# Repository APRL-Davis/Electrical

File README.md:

# Electrical
## NOTE: Legacy(2023-2024) repo - transition all continuing projects away - no new projects
Controls and data acquisition systems for Engine Mu-1+2/test stand Mu-1(v1).

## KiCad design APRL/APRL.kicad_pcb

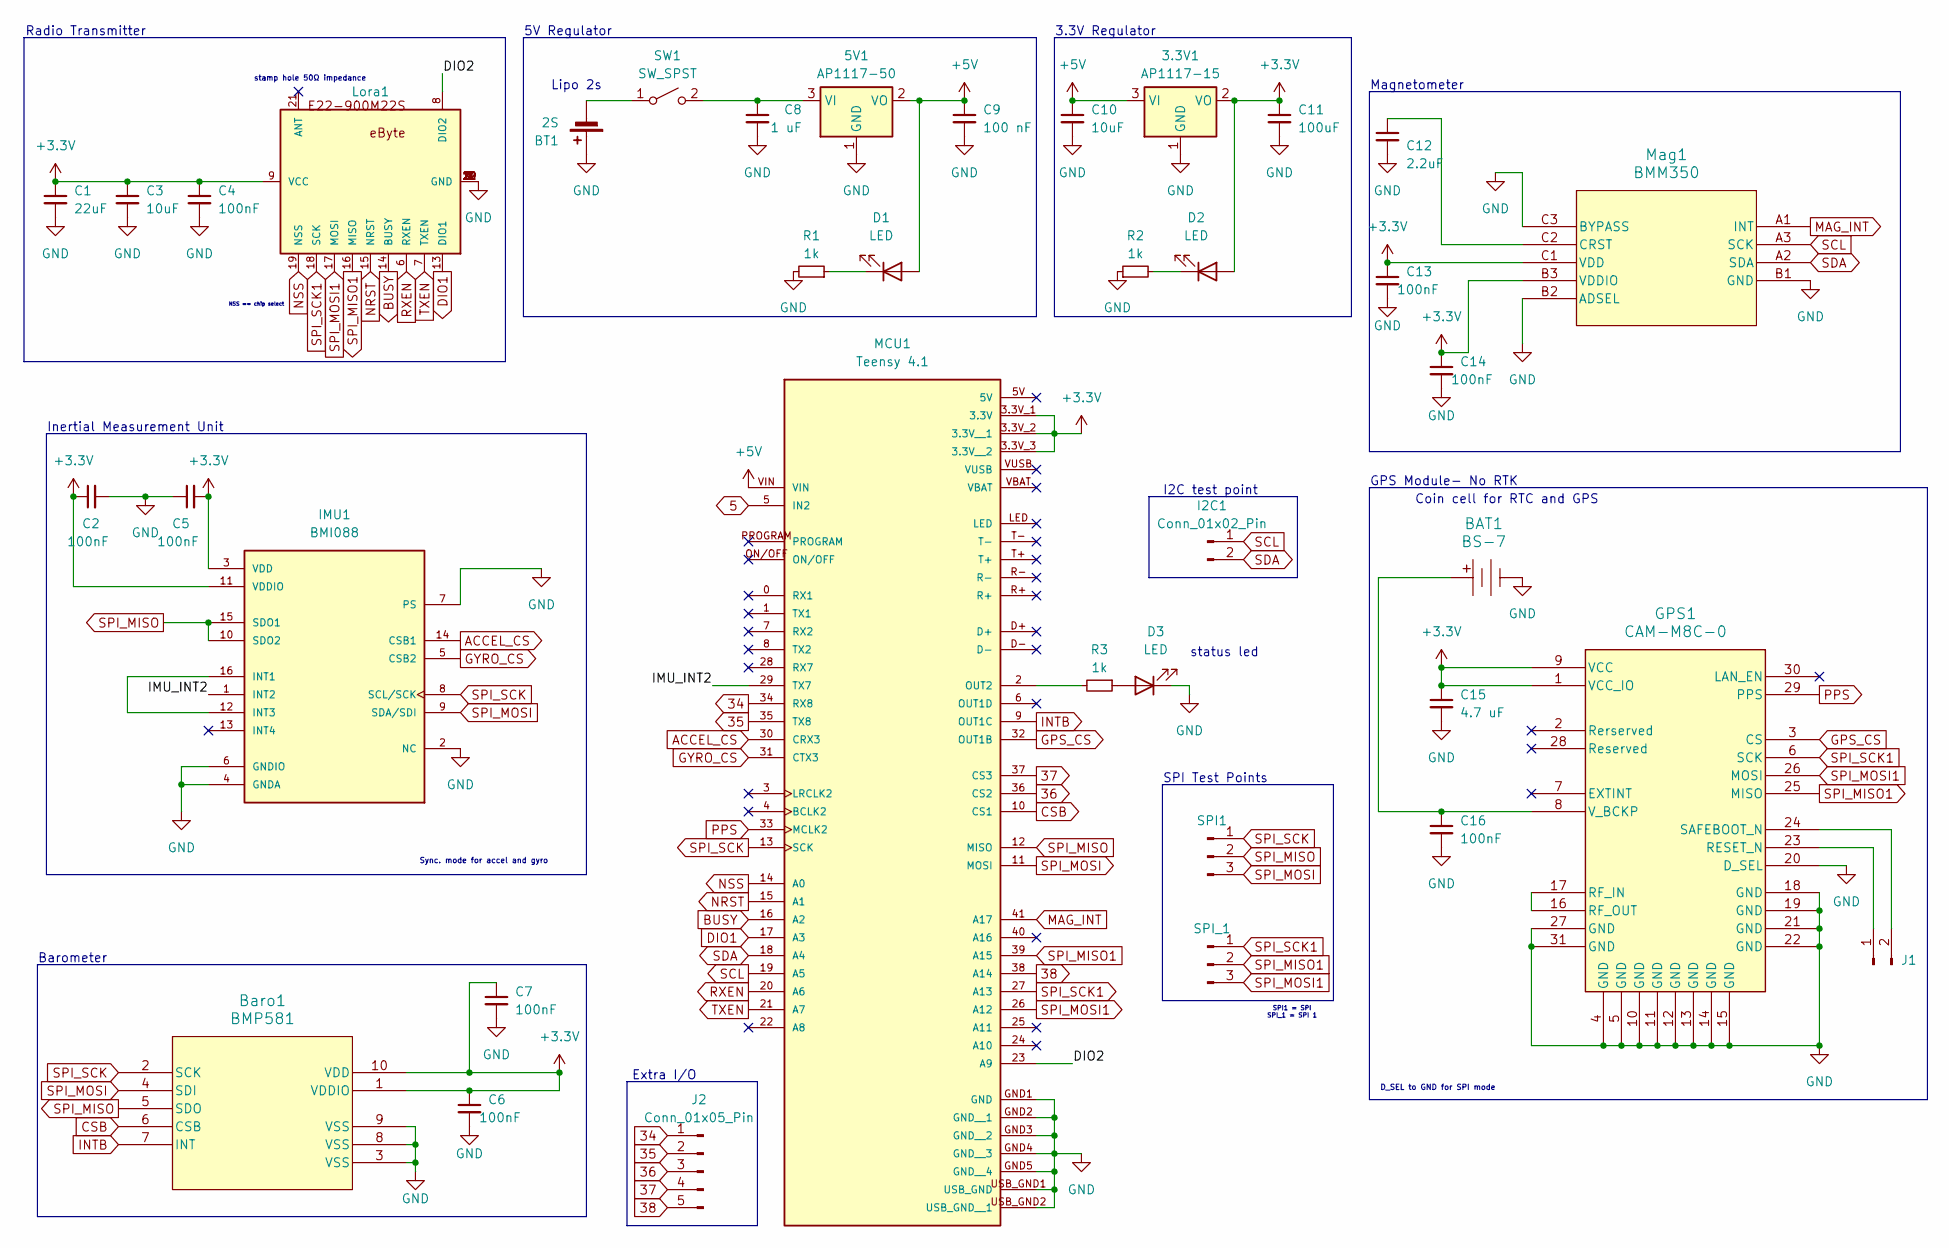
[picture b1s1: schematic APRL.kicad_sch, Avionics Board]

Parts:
3.3V1: AP1117-15; SOT-223-3_TabPin2
5V1: AP1117-50; SOT-223-3_TabPin2
BAT1: BS-7; Battery_Holder_Coin_2032_BS-7; MPN BS-7; Digi-Key_PN BS-7-ND
BT1: 2S; JST_PH_S2B-PH-K_1x02_P2.00mm_Horizontal
Baro1: BMP581; QFN10_BMP581_BOS
C1: 22uF; C_0805_2012Metric
C2, C4, C5, C6, C7, C13, C14, C16: 100nF; C_0603_1608Metric
C3: 10uF; C_0805_2012Metric
C8: 1 uF; C_0603_1608Metric
C9: 100 nF; C_0603_1608Metric
C10: 10uF; C_0603_1608Metric
C11: 100uF; C_0805_2012Metric
C12: 2.2uF; C_0603_1608Metric
C15: 4.7 uF; C_0603_1608Metric
D1, D2, D3: LED; LED_0603_1608Metric
GPS1: CAM-M8C-0; QFN_M8C-0_UBL
I2C1: Conn_01x02_Pin; PinHeader_1x02_P2.54mm_Vertical
IMU1: BMI088; PQFN50P450X300X100-16N
J1: Conn_01x02_Pin; PinHeader_1x02_P2.54mm_Vertical
J2: Conn_01x05_Pin; PinHeader_1x05_P2.54mm_Vertical
Lora1: E22-900M22S
MCU1: Teensy 4.1; Teensy_41; PARTREV 4.1
Mag1: BMM350; BGA9_BMM350_BOS
R1, R2, R3: 1k; R_0603_1608Metric
SPI1: Conn_01x03_Pin; PinHeader_1x03_P2.54mm_Vertical
SPI_1: Conn_01x03_Pin; PinHeader_1x03_P2.54mm_Vertical
SW1: SW_SPST; slide_sw

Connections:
5: MCU1.5 (IN2)
34: J2.1, MCU1.34 (RX8)
35: J2.2, MCU1.35 (TX8)
36: J2.3, MCU1.36 (CS2)
37: J2.4, MCU1.37 (CS3)
38: J2.5, MCU1.38 (A14)
+3.3V: 3.3V1.2 (VO), Baro1.1 (VDDIO), Baro1.10 (VDD), C1.1, C2.1, C3.1, C4.1, C5.2, C6.1, C7.1, C11.1, C13.1, C14.1, C15.1, D2.2 (A), GPS1.1 (VCC_IO), GPS1.9 (VCC), IMU1.3 (VDD), IMU1.11 (VDDIO), Lora1.9 (VCC), MCU1.3.3V_1 (3.3V), MCU1.3.3V_2 (3.3V__1), MCU1.3.3V_3 (3.3V__2), Mag1.B3 (VDDIO), Mag1.C1 (VDD)
+5V: 3.3V1.3 (VI), 5V1.2 (VO), C9.1, C10.1, D1.2 (A), MCU1.VIN
/DIO2: Lora1.8 (DIO2), MCU1.23 (A9)
/IMU_INT2: IMU1.1 (INT2), MCU1.29 (TX7)
ACCEL_CS: IMU1.14 (CSB1), MCU1.30 (CRX3)
BUSY: Lora1.14 (BUSY), MCU1.16 (A2)
CSB: Baro1.6 (CSB), MCU1.10 (CS1)
DIO1: Lora1.13 (DIO1), MCU1.17 (A3)
GND: 3.3V1.1 (GND), 5V1.1 (GND), BAT1.Neg, BT1.1 (+), Baro1.3 (VSS), Baro1.8 (VSS), Baro1.9 (VSS), C1.2, C2.2, C3.2, C4.2, C5.1, C6.2, C7.2, C8.2, C9.2, C10.2, C11.2, C12.2, C13.2, C14.2, C15.2, C16.2, D3.1 (K), GPS1.4 (GND), GPS1.5 (GND), GPS1.10 (GND), GPS1.11 (GND), GPS1.12 (GND), GPS1.13 (GND), GPS1.14 (GND), GPS1.15 (GND), GPS1.18 (GND), GPS1.19 (GND), GPS1.20 (D_SEL), GPS1.21 (GND), GPS1.22 (GND), GPS1.27 (GND), GPS1.31 (GND), IMU1.2 (NC), IMU1.4 (GNDA), IMU1.6 (GNDIO), IMU1.7 (PS), Lora1.1 (GND), Lora1.2 (GND), Lora1.3 (GND), Lora1.4 (GND), Lora1.5 (GND), Lora1.10 (GND), Lora1.11 (GND), Lora1.12 (GND), Lora1.20 (GND), Lora1.22 (GND), MCU1.GND1 (GND), MCU1.GND2 (GND__1), MCU1.GND3 (GND__2), MCU1.GND4 (GND__3), MCU1.GND5 (GND__4), MCU1.USB_GND1 (USB_GND), MCU1.USB_GND2 (USB_GND__1), Mag1.B1 (GND), Mag1.B2 (ADSEL), Mag1.C3 (BYPASS), R1.2, R2.1
GPS_CS: GPS1.3 (CS), MCU1.32 (OUT1B)
GYRO_CS: IMU1.5 (CSB2), MCU1.31 (CTX3)
INTB: Baro1.7 (INT), MCU1.9 (OUT1C)
MAG_INT: MCU1.41 (A17), Mag1.A1 (INT)
NRST: Lora1.15 (NRST), MCU1.15 (A1)
NSS: Lora1.19 (NSS), MCU1.14 (A0)
unnamed: 5V1.3 (VI), C8.1, SW1.2 (B)
unnamed: BT1.2 (-), SW1.1 (A)
unnamed: D1.1 (K), R1.1
unnamed: D2.1 (K), R2.2
unnamed: D3.2 (A), R3.1
unnamed: GPS1.23 (RESET_N), J1.1
unnamed: GPS1.16 (RF_OUT), GPS1.17 (RF_IN)
unnamed: GPS1.24 (SAFEBOOT_N), J1.2
unnamed: BAT1.Pos, C16.1, GPS1.8 (V_BCKP)
unnamed: IMU1.12 (INT3), IMU1.16 (INT1)
unnamed: MCU1.2 (OUT2), R3.2
unnamed: C12.1, Mag1.C2 (CRST)
PPS: GPS1.29 (PPS), MCU1.33 (MCLK2)
RXEN: Lora1.6 (RXEN), MCU1.20 (A6)
SCL: I2C1.1, MCU1.19 (A5), Mag1.A3 (SCK)
SDA: I2C1.2, MCU1.18 (A4), Mag1.A2 (SDA)
SPI_MISO: Baro1.5 (SDO), IMU1.10 (SDO2), IMU1.15 (SDO1), MCU1.12 (MISO), SPI1.2
SPI_MISO1: GPS1.25 (MISO), Lora1.16 (MISO), MCU1.39 (A15), SPI_1.2
SPI_MOSI: Baro1.4 (SDI), IMU1.9 (SDA/SDI), MCU1.11 (MOSI), SPI1.3
SPI_MOSI1: GPS1.26 (MOSI), Lora1.17 (MOSI), MCU1.26 (A12), SPI_1.3
SPI_SCK: Baro1.2 (SCK), IMU1.8 (SCL/SCK), MCU1.13 (SCK), SPI1.1
SPI_SCK1: GPS1.6 (SCK), Lora1.18 (SCK), MCU1.27 (A13), SPI_1.1
TXEN: Lora1.7 (TXEN), MCU1.21 (A7)

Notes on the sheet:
Barometer
SPI Test Points
NSS == chip select
Inertial Measurement Unit
Sync. mode for accel and gyro
Lipo 2s
status led
Coin cell for RTC and GPS
SPI1 = SPI SPI_1 = SPI 1
Magnetometer
3.3V Regulator
GPS Module- No RTK
Radio Transmitter
D_SEL to GND for SPI mode
I2C test point
5V Regulator
Extra I/O
stamp hole 50Ω impedance

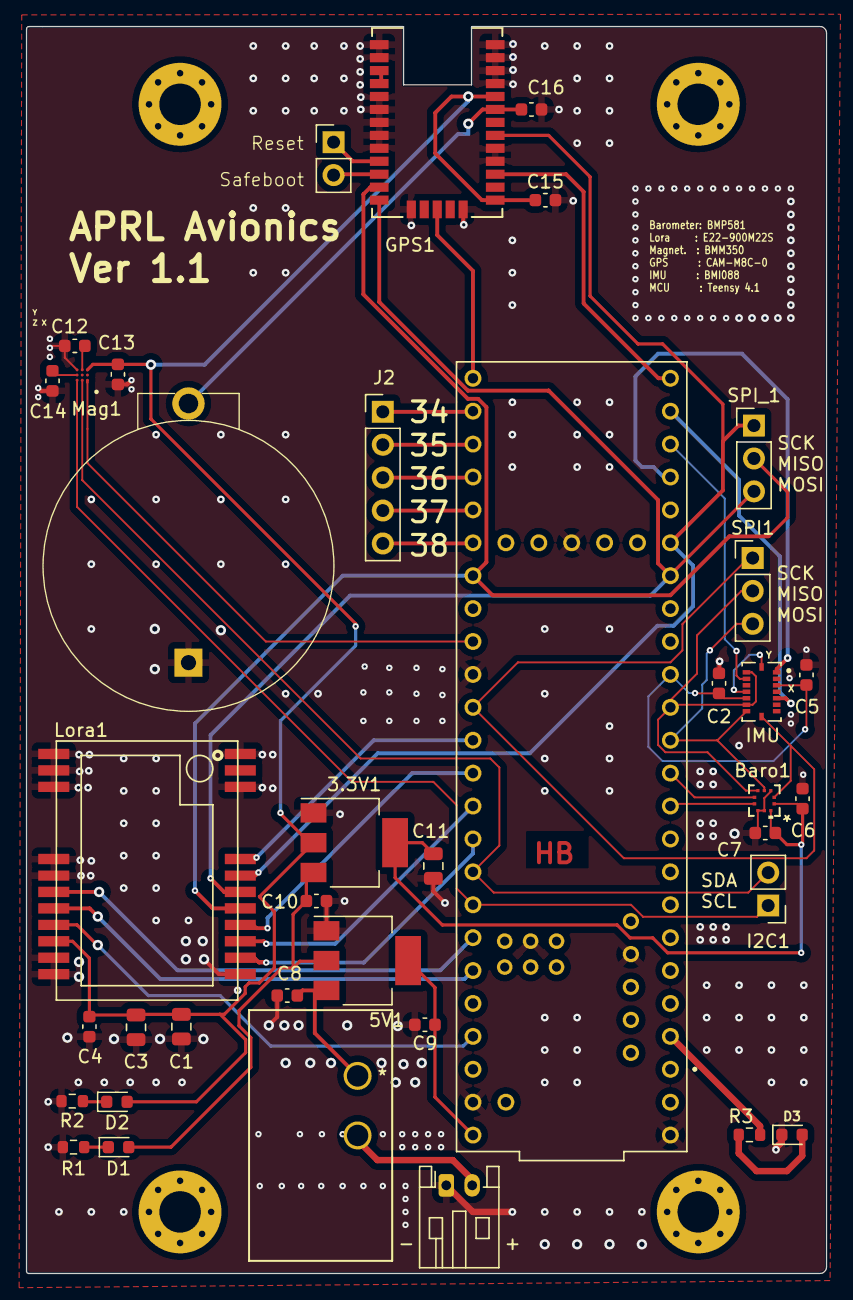
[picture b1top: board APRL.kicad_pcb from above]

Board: 2 copper layers, 61.8 x 96.2 mm, 38 parts (0 on the bottom side), 43 nets.

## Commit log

2023-10-10 Added PID files
2023-10-15 Older works
2023-10-15 add calibration, start, and stop sequence
2023-10-15 add sequences functions to switch statement
2023-10-19 add interrupt routine to control relay sequences
2023-10-19 change pin numbers
2023-10-19 fixed syntax bugs and add random number to print out for testing purposes
2023-10-19 change the reference previous time of millis function when interrupt trigger detected
2023-10-22 fix bugs in switch cases
2023-10-23 Add toggle state through another digital out pins instead of buttons; change interrupt mode to CHANGE from FALLING
2023-10-23 Add serial print statuses
2023-10-31 Modified sensor reading to use interrupts
    - Added a timer with ISR that sets a boolean flag to indicate if the main loop should read in the sensors or not.
    - Modified the end of loop delay from 10 milliseconds (~10 sensor readings) down to 50 microseconds (enough time that the idle process can still run if there is one on Teensy)
2023-11-05 new pin assignments
2023-11-10 upload old backend code
2023-11-14 Set up header file and basic functions for ADS1256
2023-11-19 unimportant change. Baud rate is ignored by Teensy. Actual rate is USB speed.
2023-11-20 starting on sensor struct type
2023-11-20 modifications to sensor reads...
2023-11-20 Added sensor configuration and types
    Also moved the Master.ino file into an appropriately named folder for the Arduino IDE.
    Made a number of updates to the code so that it will compile. No guarantees that it will run correctly.
    Also setup the data packet structures.
2023-11-21 minor structure fixes
2023-12-03 consolidate adc and relay control code
2023-12-03 folder organization
2024-01-08 fixed interrupt, where serial messes with SPI transfer
2024-01-10 fixed serial lagging issue. Make sure serial.read and parseInt occur after serial available
2024-01-17 adding no interrupts during spi transfer
2024-01-19 change data rate to 2000
2024-01-21 01/21/2024 Added purge valve but slow serial again
2024-01-21 Clarify relay and sequences states
2024-01-22 01/22/2024 Updated sequences to factor in new explicit state changes from #9ae741e
2024-01-30 avionics schematics
2024-01-30 Updated Teensy code with changes from #9ae741 (#5)
    * 01/21/2024 Added purge valve but slow serial again
    * 01/22/2024 Updated sequences to factor in new explicit state changes from #9ae741e
2024-02-05 fixed purge timing
2024-02-06 integrating udp and data packinging code from Ben
2024-02-11 Move data transmission to udp. Convert to micro volts and truncate to avoid fixed point.
2024-02-12 add kero scale
2024-02-13 automatically calculate readings per packet based on udp frequency, total sps, and number of sensors. Get rid of sensorData ID
2024-02-19 add time stamps using time library. Mirror commands to main branch. Accept incoming UDP packet for command instead of using Serial. Set port to 21 for standard FTP.
2024-02-24 switch to QNEthernet library and set up python script for client side
2024-02-24 use memset instead of pointer address for udp.begin
2024-02-25 import ti example library template
2024-02-25 update gitignore
2024-02-25 cleanup main
2024-02-25 add link status check in setup
2024-02-25 integrate UDP to main wwith dummy test data
2024-02-25 complete hal.h for teensy, hal.c done up to getStart
2024-02-25 apparently i didn't push
2024-02-27 finish hal.c
2024-02-27 finished modifying library
2024-02-28 cleanup also rename c to cpp
2024-03-01 parse command inputs from udp; add depressurize command; removes depressurize from purge; remove auto purge from fire sequence.
2024-03-06 disable serial check loop to prevent blocking when not connected to computer
2024-03-06 send back valve states
2024-03-06 get rid of dangling pointer in the conversion method. Dynamically allocate memory outside and pass into the function so it doesn't self destruct
2024-03-06 add check sum to detect valve state changes
2024-03-07 attempt merging devop - add static fire mvp changes (#7)
    * integrating udp and data packinging code from Ben
    * Move data transmission to udp. Convert to micro volts and truncate to avoid fixed point.
    * add kero scale
    * automatically calculate readings per packet based on udp frequency, total sps, and number of sensors. Get rid of sensorData ID
    * add time stamps using time library. Mirror commands to main branch. Accept incoming UDP packet for command instead of using Serial. Set port to 21 for standard FTP.
    * switch to QNEthernet library and set up python script for client side
2024-03-07 get rid of checksum loop that detect valve state changes. Directly detect changes when relay is toggle or sequence invoked
2024-03-15 Added encoder readings to data stream
2024-03-18 fix compiler warning, add board bringup test code
2024-03-18 working test config, rename crc.c to crc.cpp
2024-04-01 back from break
2024-04-04 implement state machine and modify buffer shifting conversion function.
2024-04-04 changing network configs
2024-04-06 fars
2024-04-12 state machine broke
2024-04-18 read 4 load cells and send over udp
2024-04-18 working, cleanup a little
2024-04-23 current working state machine, no load cells
2024-04-23 working state machine
2024-06-16 change firetime to 5s and kero delay to 0s
2024-06-21 schematics
2024-06-26 revision 1 of avionics board
2024-11-01 Update README.md to reflect legacy nature of this repo
    This repo was used last year(2023-2024), but going forward, we will organize our projects better in separate repos. As of now, we have begun to transition continuing projects to new repos, and this r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
2024-11-15 Redone state machine can do auto firing sequence, still need to code manual
2024-11-22 Finished re-writing state machine, just need to test
2025-04-12 UNTESTED: quick fix to add timestamp to valvestate packets
2025-04-14 UNTESTED: move valve state timestamp block to reflect actual order, see previous commit about adding this timestamp
